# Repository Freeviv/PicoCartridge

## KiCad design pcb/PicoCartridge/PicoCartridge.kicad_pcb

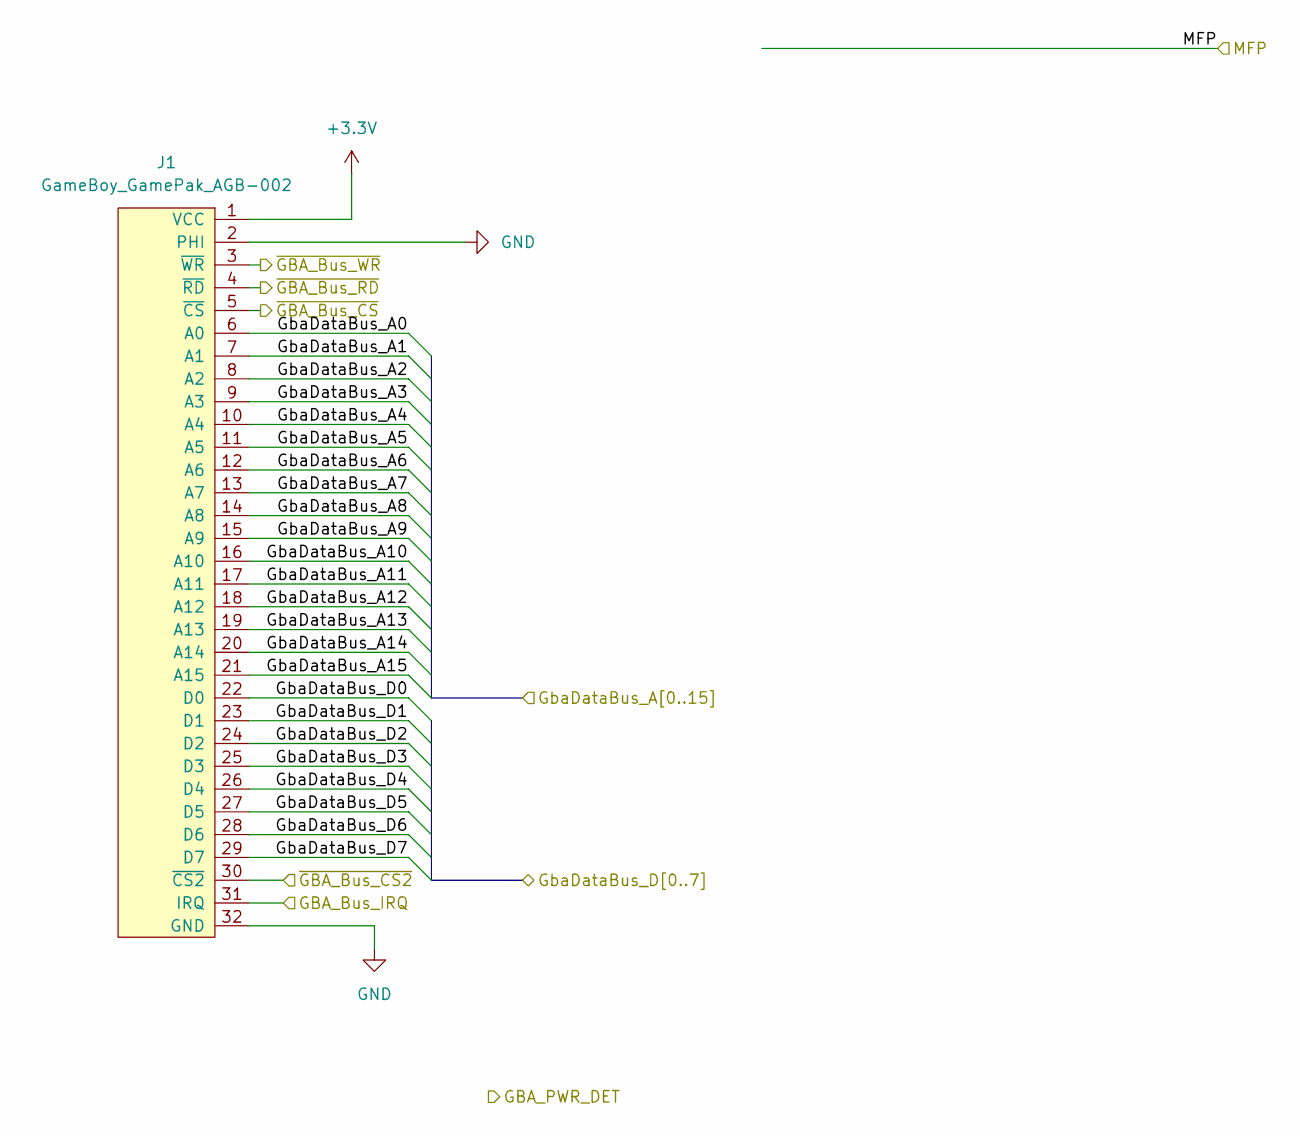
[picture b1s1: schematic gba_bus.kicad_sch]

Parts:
J1: GameBoy_GamePak_AGB-002; GameBoy_GamePak_AGB-002_P1.50mm_Edge

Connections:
+3.3V: J1.1 (VCC); also elsewhere on the board
/GBA Bus/GbaDataBus_A0: J1.6 (A0); also elsewhere on the board
/GBA Bus/GbaDataBus_A1: J1.7 (A1); also elsewhere on the board
/GBA Bus/GbaDataBus_A2: J1.8 (A2); also elsewhere on the board
/GBA Bus/GbaDataBus_A3: J1.9 (A3); also elsewhere on the board
/GBA Bus/GbaDataBus_A4: J1.10 (A4); also elsewhere on the board
/GBA Bus/GbaDataBus_A5: J1.11 (A5); also elsewhere on the board
/GBA Bus/GbaDataBus_A6: J1.12 (A6); also elsewhere on the board
/GBA Bus/GbaDataBus_A7: J1.13 (A7); also elsewhere on the board
/GBA Bus/GbaDataBus_A8: J1.14 (A8); also elsewhere on the board
/GBA Bus/GbaDataBus_A9: J1.15 (A9); also elsewhere on the board
/GBA Bus/GbaDataBus_A10: J1.16 (A10); also elsewhere on the board
/GBA Bus/GbaDataBus_A11: J1.17 (A11); also elsewhere on the board
/GBA Bus/GbaDataBus_A12: J1.18 (A12); also elsewhere on the board
/GBA Bus/GbaDataBus_A13: J1.19 (A13); also elsewhere on the board
/GBA Bus/GbaDataBus_A14: J1.20 (A14); also elsewhere on the board
/GBA Bus/GbaDataBus_A15: J1.21 (A15); also elsewhere on the board
/GBA Bus/GbaDataBus_D0: J1.22 (D0); also elsewhere on the board
/GBA Bus/GbaDataBus_D1: J1.23 (D1); also elsewhere on the board
/GBA Bus/GbaDataBus_D2: J1.24 (D2); also elsewhere on the board
/GBA Bus/GbaDataBus_D3: J1.25 (D3); also elsewhere on the board
/GBA Bus/GbaDataBus_D4: J1.26 (D4); also elsewhere on the board
/GBA Bus/GbaDataBus_D5: J1.27 (D5); also elsewhere on the board
/GBA Bus/GbaDataBus_D6: J1.28 (D6); also elsewhere on the board
/GBA Bus/GbaDataBus_D7: J1.29 (D7); also elsewhere on the board
/MCU/GBA_Bus_IRQ: J1.31 (IRQ); also elsewhere on the board
/MCU/~GBA_Bus_CS2: J1.30 (~CS2); also elsewhere on the board
/MCU/~GBA_Bus_CS: J1.5 (~CS); also elsewhere on the board
/MCU/~GBA_Bus_RD: J1.4 (~RD); also elsewhere on the board
/MCU/~GBA_Bus_WR: J1.3 (~WR); also elsewhere on the board
GND: J1.2 (PHI), J1.32 (GND); also elsewhere on the board

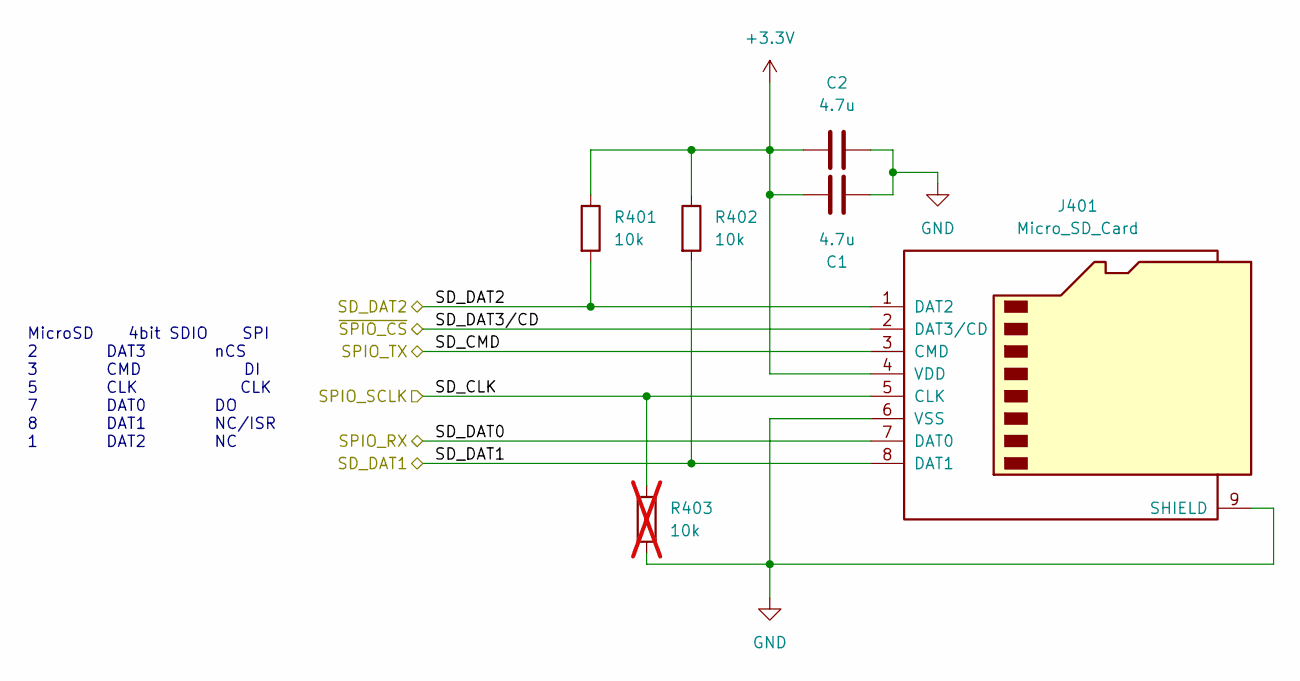
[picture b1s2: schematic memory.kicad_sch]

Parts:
C1, C2: 4.7u; C_0402_1005Metric
J401: Micro_SD_Card; microSD_HC_Molex_104031-0811
R401, R402: 10k; R_0402_1005Metric
R403: 10k; R_0402_1005Metric; not fitted

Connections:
+3.3V: C1.1, C2.2, J401.4 (VDD), R401.1, R402.1; also elsewhere on the board
/MCU/SD_DAT1: J401.8 (DAT1), R402.2; also elsewhere on the board
/MCU/SD_DAT2: J401.1 (DAT2), R401.2; also elsewhere on the board
/MCU/SPI0_RX: J401.7 (DAT0); also elsewhere on the board
/MCU/SPI0_SCLK: J401.5 (CLK), R403.1; also elsewhere on the board
/MCU/SPI0_TX: J401.3 (CMD); also elsewhere on the board
/MCU/~SPI0_CS: J401.2 (DAT3/CD); also elsewhere on the board
GND: C1.2, C2.1, J401.6 (VSS), J401.9 (SHIELD), R403.2; also elsewhere on the board

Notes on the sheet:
MicroSD 4bit SDIO SPI 2 DAT3 nCS 3 CMD DI 5 CLK CLK 7 DAT0 DO 8 DAT1 NC/ISR 1 DAT2 NC

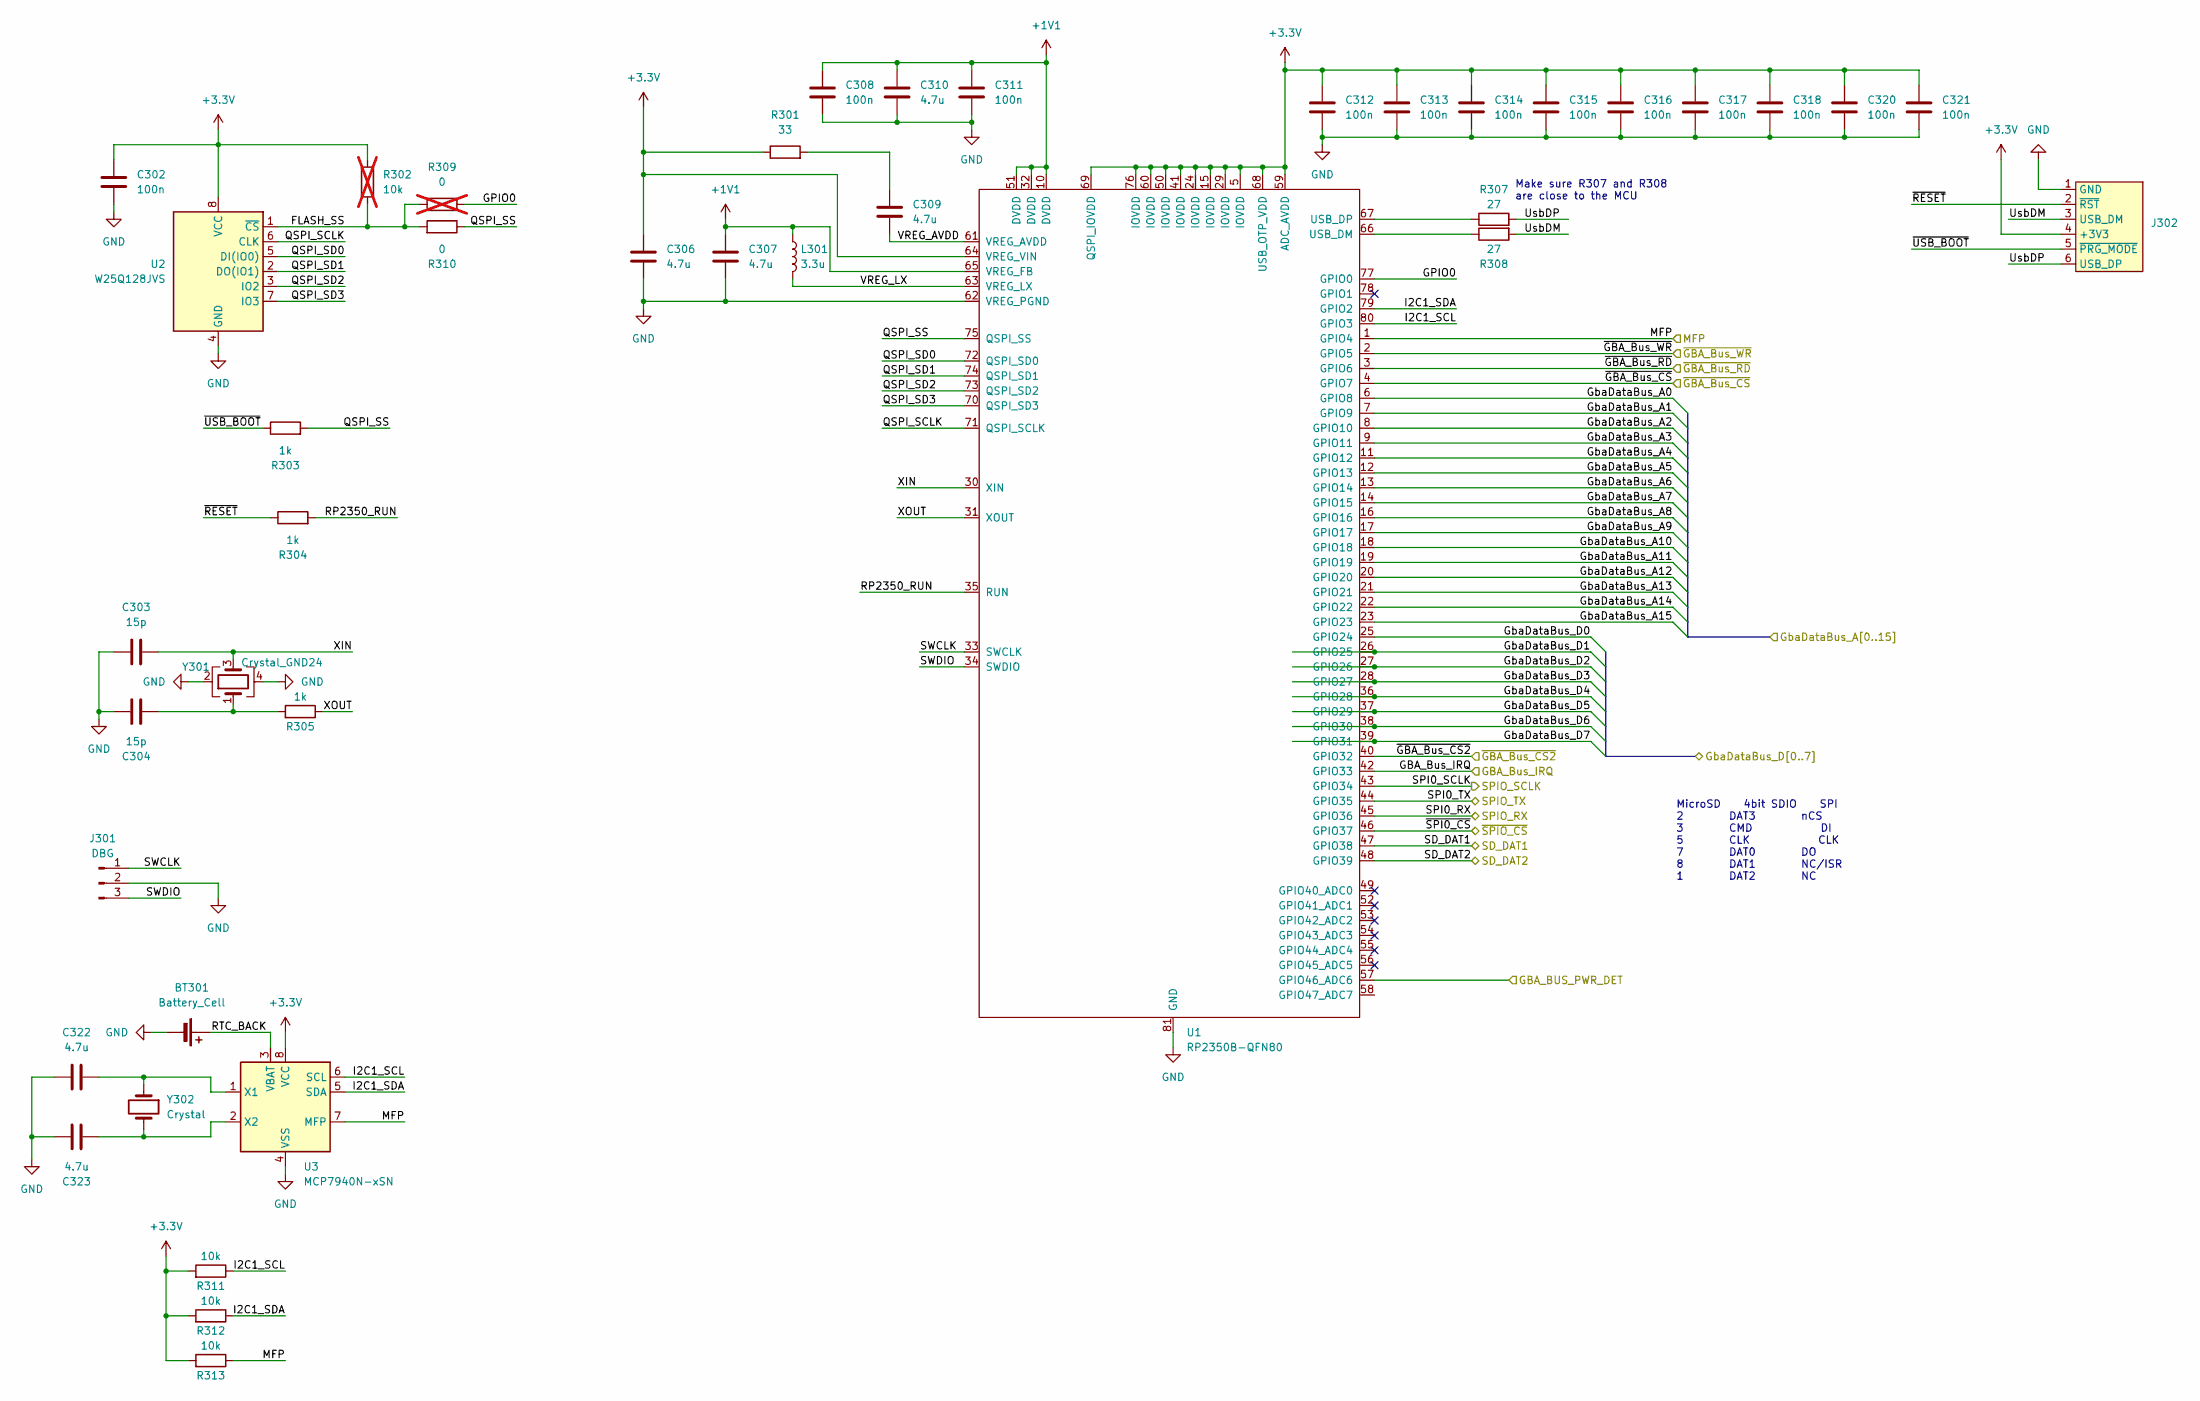
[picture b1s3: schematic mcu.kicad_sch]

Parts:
BT301: Battery_Cell
C302, C308, C311, C312, C313, C314, C315, C316, C317, C318, C320, C321: 100n; C_0402_1005Metric
C303, C304: 15p; C_0402_1005Metric
C306, C307, C309, C310, C322, C323: 4.7u; C_0402_1005Metric
J301: DBG; PinHeader_1x03_P1.27mm_Vertical
J302: ProgrammerConnector_SMD
L301: 3.3u
R301: 33; R_0402_1005Metric
R302: 10k; R_0402_1005Metric; not fitted
R303, R304, R305: 1k; R_0402_1005Metric
R307, R308: 27; R_0402_1005Metric
R309: 0; R_0402_1005Metric; not fitted
R310: 0; R_0402_1005Metric
R311, R312, R313: 10k; R_0402_1005Metric
U1: RP2350B-QFN80; RP2350B_QFN-80_EP_10.573x10.573_Pitch0.4mm
U2: W25Q128JVS; SOIC-8_5.23x5.23mm_P1.27mm
U3: MCP7940N-xSN; SOIC-8_3.9x4.9mm_P1.27mm
Y301: Crystal_GND24
Y302: Crystal; Crystal_DS26_D2.0mm_L6.0mm_Horizontal; LCSC# C2681251

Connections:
+1V1: C307.1, C308.1, C310.1, C311.1, L301.1, U1.10 (DVDD), U1.32 (DVDD), U1.51 (DVDD), U1.65 (VREG_FB)
+3.3V: C302.1, C306.1, C312.1, C313.1, C314.1, C315.1, C316.1, C317.1, C318.1, C320.1, C321.1, J302.4 (+3V3), R301.1, R302.1, R311.2, R312.2, R313.2, U1.5 (IOVDD), U1.15 (IOVDD), U1.24 (IOVDD), U1.29 (IOVDD), U1.41 (IOVDD), U1.50 (IOVDD), U1.59 (ADC_AVDD), U1.60 (IOVDD), U1.64 (VREG_VIN), U1.68 (USB_OTP_VDD), U1.69 (QSPI_IOVDD), U1.76 (IOVDD), U2.8 (VCC), U3.8 (VCC); also elsewhere on the board
/GBA Bus/GBA_PWR_DET: U1.57 (GPIO46_ADC6)
/GBA Bus/GbaDataBus_A0: U1.6 (GPIO8); also elsewhere on the board
/GBA Bus/GbaDataBus_A1: U1.7 (GPIO9); also elsewhere on the board
/GBA Bus/GbaDataBus_A2: U1.8 (GPIO10); also elsewhere on the board
/GBA Bus/GbaDataBus_A3: U1.9 (GPIO11); also elsewhere on the board
/GBA Bus/GbaDataBus_A4: U1.11 (GPIO12); also elsewhere on the board
/GBA Bus/GbaDataBus_A5: U1.12 (GPIO13); also elsewhere on the board
/GBA Bus/GbaDataBus_A6: U1.13 (GPIO14); also elsewhere on the board
/GBA Bus/GbaDataBus_A7: U1.14 (GPIO15); also elsewhere on the board
/GBA Bus/GbaDataBus_A8: U1.16 (GPIO16); also elsewhere on the board
/GBA Bus/GbaDataBus_A9: U1.17 (GPIO17); also elsewhere on the board
/GBA Bus/GbaDataBus_A10: U1.18 (GPIO18); also elsewhere on the board
/GBA Bus/GbaDataBus_A11: U1.19 (GPIO19); also elsewhere on the board
/GBA Bus/GbaDataBus_A12: U1.20 (GPIO20); also elsewhere on the board
/GBA Bus/GbaDataBus_A13: U1.21 (GPIO21); also elsewhere on the board
/GBA Bus/GbaDataBus_A14: U1.22 (GPIO22); also elsewhere on the board
/GBA Bus/GbaDataBus_A15: U1.23 (GPIO23); also elsewhere on the board
/GBA Bus/GbaDataBus_D0: U1.25 (GPIO24); also elsewhere on the board
/GBA Bus/GbaDataBus_D1: U1.26 (GPIO25); also elsewhere on the board
/GBA Bus/GbaDataBus_D2: U1.27 (GPIO26); also elsewhere on the board
/GBA Bus/GbaDataBus_D3: U1.28 (GPIO27); also elsewhere on the board
/GBA Bus/GbaDataBus_D4: U1.36 (GPIO28); also elsewhere on the board
/GBA Bus/GbaDataBus_D5: U1.37 (GPIO29); also elsewhere on the board
/GBA Bus/GbaDataBus_D6: U1.38 (GPIO30); also elsewhere on the board
/GBA Bus/GbaDataBus_D7: U1.39 (GPIO31); also elsewhere on the board
/GBA Bus/MFP: R313.1, U1.1 (GPIO4), U3.7 (MFP)
/MCU/FLASH_SS: R302.2, R309.2, R310.2, U2.1 (~CS)
/MCU/GBA_Bus_IRQ: U1.42 (GPIO33); also elsewhere on the board
/MCU/GPIO0: R309.1, U1.77 (GPIO0)
/MCU/I2C1_SCL: R311.1, U1.80 (GPIO3), U3.6 (SCL)
/MCU/I2C1_SDA: R312.1, U1.79 (GPIO2), U3.5 (SDA)
/MCU/QSPI_SCLK: U1.71 (QSPI_SCLK), U2.6 (CLK)
/MCU/QSPI_SD0: U1.72 (QSPI_SD0), U2.5 (DI(IO0))
/MCU/QSPI_SD1: U1.74 (QSPI_SD1), U2.2 (DO(IO1))
/MCU/QSPI_SD2: U1.73 (QSPI_SD2), U2.3 (IO2)
/MCU/QSPI_SD3: U1.70 (QSPI_SD3), U2.7 (IO3)
/MCU/QSPI_SS: R303.2, R310.1, U1.75 (QSPI_SS)
/MCU/RP2350_RUN: R304.2, U1.35 (RUN)
/MCU/RTC_BACK: BT301.1 (+), U3.3 (VBAT)
/MCU/SD_DAT1: U1.47 (GPIO38); also elsewhere on the board
/MCU/SD_DAT2: U1.48 (GPIO39); also elsewhere on the board
/MCU/SPI0_RX: U1.45 (GPIO36); also elsewhere on the board
/MCU/SPI0_SCLK: U1.43 (GPIO34); also elsewhere on the board
/MCU/SPI0_TX: U1.44 (GPIO35); also elsewhere on the board
/MCU/SWCLK: J301.1, U1.33 (SWCLK)
/MCU/SWDIO: J301.3, U1.34 (SWDIO)
/MCU/UsbDM: J302.3 (USB_DM), R308.2
/MCU/UsbDP: J302.6 (USB_DP), R307.2
/MCU/VREG_AVDD: C309.2, U1.61 (VREG_AVDD)
/MCU/VREG_LX: L301.2, U1.63 (VREG_LX)
/MCU/XIN: C303.2, U1.30 (XIN), Y301.3
/MCU/XOUT: R305.1, U1.31 (XOUT)
/MCU/~GBA_Bus_CS2: U1.40 (GPIO32); also elsewhere on the board
/MCU/~GBA_Bus_CS: U1.4 (GPIO7); also elsewhere on the board
/MCU/~GBA_Bus_RD: U1.3 (GPIO6); also elsewhere on the board
/MCU/~GBA_Bus_WR: U1.2 (GPIO5); also elsewhere on the board
/MCU/~RESET: J302.2 (~RST), R304.1
/MCU/~SPI0_CS: U1.46 (GPIO37); also elsewhere on the board
/MCU/~USB_BOOT: J302.5 (~PRG_MODE), R303.1
GND: BT301.2 (-), C302.2, C303.1, C304.1, C306.2, C307.2, C308.2, C310.2, C311.2, C312.2, C313.2, C314.2, C315.2, C316.2, C317.2, C318.2, C320.2, C321.2, C322.1, C323.1, J301.2, J302.1 (GND), U1.62 (VREG_PGND), U1.81 (GND), U2.4 (GND), U3.4 (VSS), Y301.2, Y301.4; also elsewhere on the board
unnamed: C304.2, R305.2, Y301.1
unnamed: C309.1, R301.2
unnamed: R308.1, U1.66 (USB_DM)
unnamed: R307.1, U1.67 (USB_DP)
unnamed: C322.2, U3.1 (X1), Y302.1
unnamed: C323.2, U3.2 (X2), Y302.2

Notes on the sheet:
Make sure R307 and R308 are close to the MCU
MicroSD 4bit SDIO SPI 2 DAT3 nCS 3 CMD DI 5 CLK CLK 7 DAT0 DO 8 DAT1 NC/ISR 1 DAT2 NC

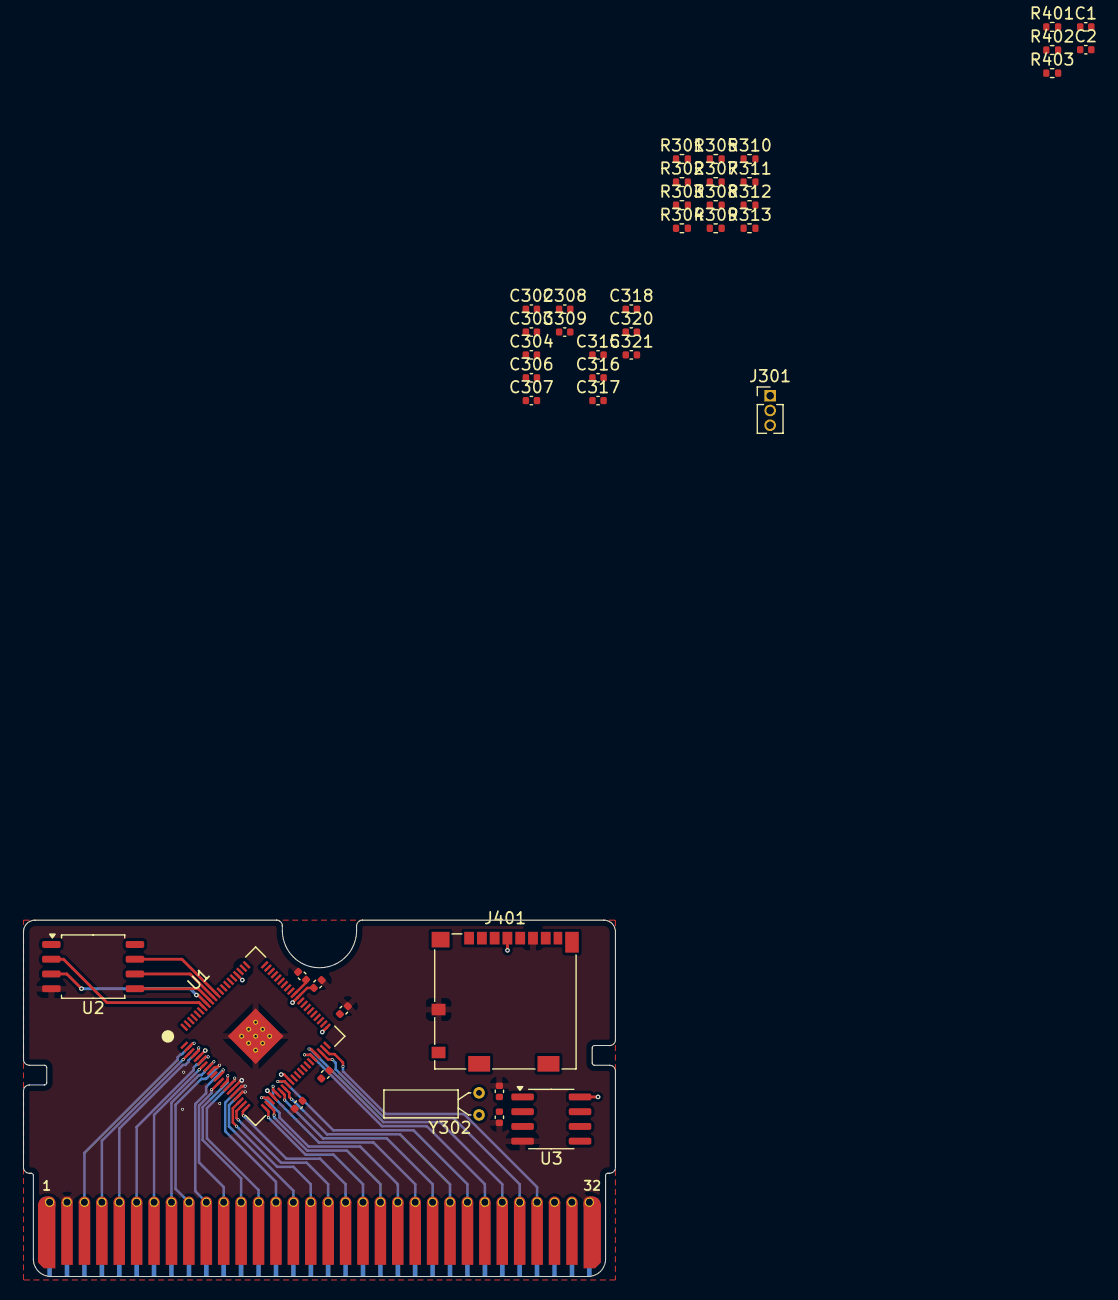
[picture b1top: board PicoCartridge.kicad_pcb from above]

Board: 4 copper layers, 51.0 x 30.7 mm, 45 parts (0 on the bottom side), 65 nets.

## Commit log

2024-08-31 Added inital project
2024-09-01 Added RP2350 circuitry
2024-09-05 Defined additional interfaces
2024-09-05 Added base pcb layout
2024-09-05 Very basic setup
2024-10-03 Added nets from main sheet
2024-10-04 Initial sdk setup
2024-10-05 Fixed connection between MCU and SD card
2024-10-07 Added lock file to ignored files
2024-10-07 Fixed GBA bus internal logic
    THe GBA bus is now a correct bus in a sense of kicad
2024-10-08 Removed dedicated usb connector
    Use would be very limited (live view on a pc and data transfer without
    removing the sd card) and increases the pcb & schematic complexity by a lot.
    Removing the usb connector for this revision. It is possible, if this design
    is successful that I will create a new revision at some point. You never know.
2024-10-08 Added programmer "connector"
    Additionally removed reset and program switches as there is no need for
    them on the pcb itself if there is no usb connection.
2024-10-08 Added programmer connection (#4)
    * Removed dedicated usb connector
    Use would be very limited (live view on a pc and data transfer without
    removing the sd card) and increases the pcb & schematic complexity by a lot.
    Removing the usb connector for this revision. It is possible, if this design
    is successful that I will create a new revision at some point. You never know.
    * Added programmer "connector"
2024-12-09 Upload progress
